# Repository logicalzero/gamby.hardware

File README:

gamby.hardware README
=====================

This repository contains the EAGLE files for the GAMBY LCD/Game shield for
Arduino.

If anyone is interested in porting the design over to a non-proprietary
format (e.g. gEDA), please contact me! 

Design Notes
------------

* Every Arduino pin has a second pad. These pads conform to a uniform .1"
spacing, correcting the .05" offset of the header for digital I/O pins 
8-13 and GND/AREF.

* Although it uses the same pins, this design does not use the ATMega's 
built-in SPI. Since this device does not support bidirectional communication,
using the built-in SPI would have wasted a pin; it would have overly
complicated the traces as well.

* The traces between all of the 'used' Arduino pins and the second pad
have been left uncovered by the bottom soldermask. This is to make it
easier to cut the traces should the user want to rewire things --
to make use of the hardware SPI, for example.

Thanks
------

Thanks go out to my fellow Boston dorkbotter, Tim, for reverse engineering
the surplus LCD module.

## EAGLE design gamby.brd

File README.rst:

gamby.hardware README
=====================

This repository contains the EAGLE files for the GAMBY LCD/Game shield for
Arduino.

If anyone is interested in porting the design over to a non-proprietary
format (e.g. gEDA), please contact me! 

Design Notes
------------

* Every Arduino pin has a second pad. These pads conform to a uniform .1" spacing, correcting the .05" offset of the header for digital I/O pins 8-13 and GND/AREF.

* Although it uses the same pins, this design does not use the ATMega's built-in SPI. Since this device does not support bidirectional communication, using the built-in SPI would have wasted a pin; it would have overly complicated the traces as well.

* The traces between all of the 'used' Arduino pins and the second pad have been left uncovered by the bottom soldermask. This is to make it easier to cut the traces should the user want to rewire things -- to make use of the hardware SPI, for example.

* The sound, D-Pad and buttons have pads for headers; the pads are shorted by a thin, uncovered trace. The sound and inputs can be disabled by cutting this trace, then re-enabled by adding a 2-pin header (3 pins, in the case of sound) and a jumper.

Prototypes
----------

The items in the prototypes directory are the versions that were sent for 
short-run fabrication. The pin-out of the first prototype differs from
the new version. The second prototype has a few minor adjustments made
to make it compatible with the fabrication service (0.1" milling bit,
etc.). 

Datasheets
----------

* LCD: Samsung UG09B63-FLGT4AA using `S6B0755 LCD Controller <http://www.alldatasheet.com/datasheet-pdf/pdf/37866/SAMSUNG/S6B0755.html>`__ or compatible (some features unsupported)
* D-Pad: `ALPS SKQAAA010 4-direction switch <http://www.alldatasheet.com/datasheet-pdf/pdf/329112/ALPS/SKQU.html>`__
* Piezo speaker: `TDK PS1240P02BT <http://www.alldatasheet.com/datasheet-pdf/pdf/349367/TDK/PS1720P02.html>`__
* Backlight LEDs: `Dialight 598-8340-107F <http://www.dialight.com/Assets%5CBrochures_And_Catalogs%5CIndication%5CMDEI5981208RT.pdf>`__

Thanks
------

Thanks go out to my fellow Boston dorkbotter, Tim, for reverse engineering
the surplus LCD module.

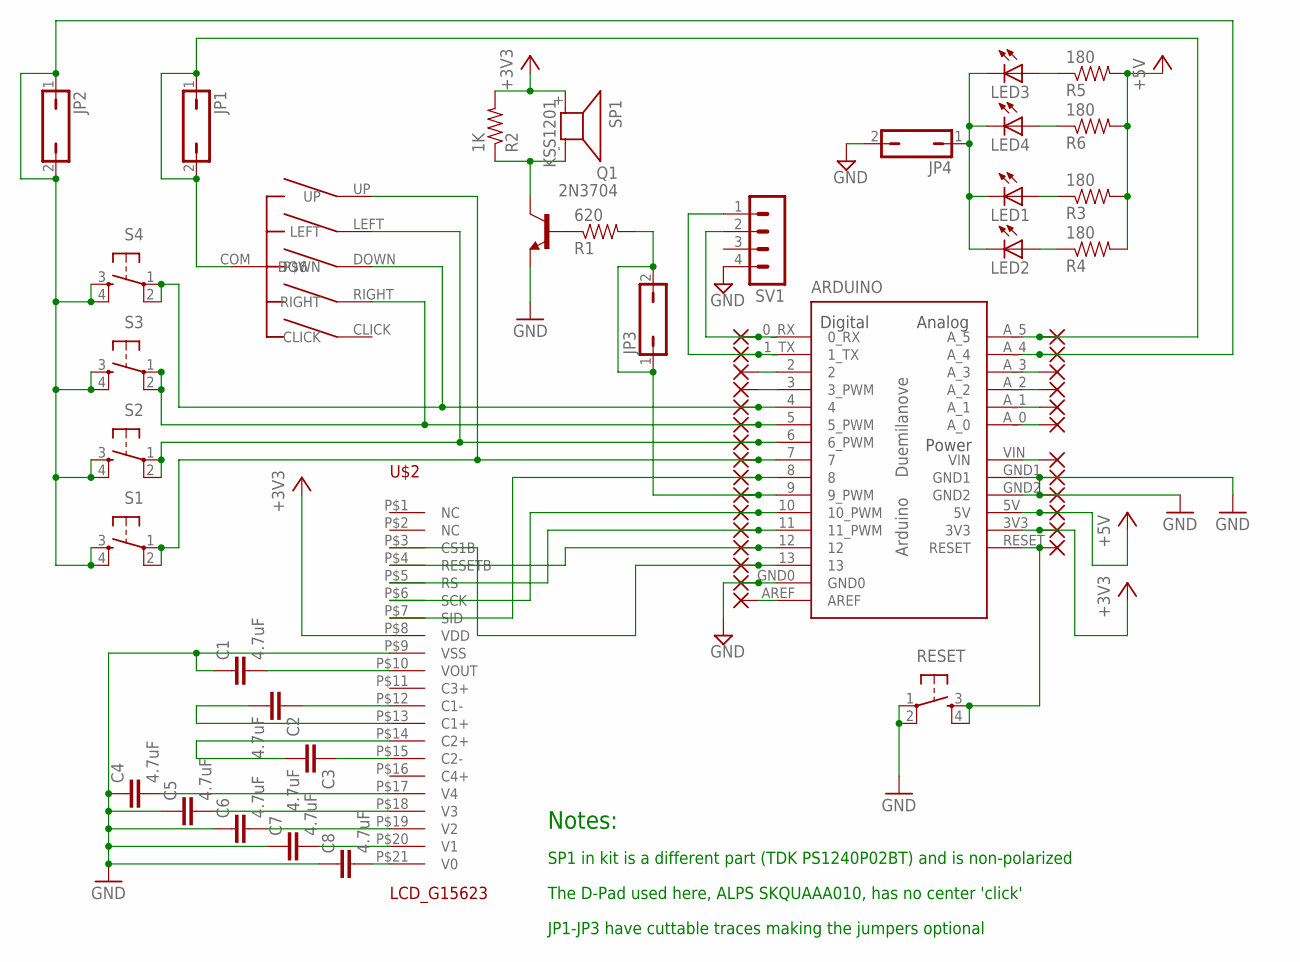
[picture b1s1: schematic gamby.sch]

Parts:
ARDUINO: ARDUINO-USBLONG_PADS_TEXT; SHIELD
C1, C2, C3, C4, C5, C6, C7, C8: 4.7uF; C2.5-2
JP1, JP2, JP3, JP4: JP1Q; JP1
LED1, LED2, LED3, LED4: LEDSMT1206; 1206
PAD_3V3, PAD_5V: WIREPAD1,6/0,9; 1,6/0,9
PAD_A0, PAD_A1, PAD_A2, PAD_A3, PAD_A4, PAD_A5: WIREPAD1,6/0,9; 1,6/0,9
PAD_AREF: WIREPAD1,6/0,9; 1,6/0,9
PAD_D2, PAD_D3, PAD_D4, PAD_D5, PAD_D6, PAD_D7, PAD_D8, PAD_D9, PAD_D10, PAD_D11, PAD_D12, PAD_D13: WIREPAD1,6/0,9; 1,6/0,9
PAD_GND0, PAD_GND1, PAD_GND2: WIREPAD1,6/0,9; 1,6/0,9
PAD_RESET: WIREPAD1,6/0,9; 1,6/0,9
PAD_RX: WIREPAD1,6/0,9; 1,6/0,9
PAD_TX: WIREPAD1,6/0,9; 1,6/0,9
PAD_VIN: WIREPAD1,6/0,9; 1,6/0,9
Q1: 2N3704; TO92
R1: 620; AXIAL-0.3
R2: 1K; AXIAL-0.3
R3, R4, R5, R6: 180; AXIAL-0.3
RESET: TAC_SWITCHPTH; TACTILE-PTH
S1, S2, S3, S4: TAC_SWITCHPTH; TACTILE-PTH
SP1: KSS1201
SV1: MA04-1
U$2: LCD_G15623
U$3: DEV1; DIP

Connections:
0_RX: ARDUINO.0_RX, PAD_RX.1, SV1.2
1_TX: ARDUINO.1_TX, PAD_TX.1, SV1.1
+3V3: ARDUINO.3V3, PAD_3V3.1, R2.P$2 (2), SP1.+ (1), U$2.P$8 (VDD)
+5V: ARDUINO.5V, PAD_5V.1, R3.P$2 (2), R4.P$2 (2), R5.P$2 (2), R6.P$2 (2)
A0: ARDUINO.A_0, PAD_A0.1
A4_BUTTONS: ARDUINO.A_4, JP2.1, JP2.2, PAD_A4.1, S1.3, S1.4, S2.3, S2.4, S3.3, S3.4, S4.3, S4.4
A5_DPAD: ARDUINO.A_5, JP1.1, JP1.2, PAD_A5.1, U$3.COM
BUTTON_A: ARDUINO.7, PAD_D7.1, S1.1, S1.2, U$3.UP
D2: ARDUINO.4, PAD_D4.1, S4.1, S4.2, U$3.DOWN
D3: ARDUINO.9 (9_PWM), JP3.1, JP3.2, PAD_D9.1, R1.P$2 (2)
D4: ARDUINO.5 (5_PWM), PAD_D5.1, S3.1, S3.2, U$3.RIGHT
D5: ARDUINO.6 (6_PWM), PAD_D6.1, S2.1, S2.2, U$3.LEFT
GND: ARDUINO.GND0, ARDUINO.GND1, ARDUINO.GND2, C1.1, C4.1, C5.1, C6.1, C7.1, C8.1, JP4.2, PAD_GND0.1, PAD_GND1.1, PAD_GND2.1, Q1.3 (E), RESET.1, RESET.2, SV1.4, U$2.P$9 (VSS)
unnamed: ARDUINO.8, PAD_D8.1, U$2.P$7 (SID)
unnamed: ARDUINO.10 (10_PWM), PAD_D10.1, U$2.P$6 (SCK)
unnamed: ARDUINO.11 (11_PWM), PAD_D11.1, U$2.P$5 (RS)
unnamed: ARDUINO.12, PAD_D12.1, U$2.P$4 (RESETB)
unnamed: LED1.A, R3.P$1 (1)
unnamed: LED2.A, R4.P$1 (1)
unnamed: JP4.1, LED1.C, LED2.C, LED3.C, LED4.C
unnamed: LED4.A, R6.P$1 (1)
unnamed: ARDUINO.VIN, PAD_VIN.1
unnamed: Q1.2 (C), R2.P$1 (1), SP1.- (2)
unnamed: Q1.1 (B), R1.P$1 (1)
unnamed: ARDUINO.3 (3_PWM), PAD_D3.1
unnamed: C7.2, U$2.P$20 (V1)
unnamed: C5.2, U$2.P$18 (V3)
unnamed: C8.2, U$2.P$21 (V0)
unnamed: C4.2, U$2.P$17 (V4)
unnamed: ARDUINO.13, PAD_D13.1, U$2.P$3 (CS1B)
unnamed: C6.2, U$2.P$19 (V2)
unnamed: ARDUINO.2, PAD_D2.1
unnamed: C3.1, U$2.P$15 (C2-)
unnamed: C3.2, U$2.P$14 (C2+)
unnamed: C2.2, U$2.P$13 (C1+)
unnamed: C2.1, U$2.P$12 (C1-)
unnamed: ARDUINO.A_1, PAD_A1.1
unnamed: C1.2, U$2.P$10 (VOUT)
unnamed: LED3.A, R5.P$1 (1)
unnamed: ARDUINO.RESET, PAD_RESET.1, RESET.3, RESET.4
unnamed: ARDUINO.A_2, PAD_A2.1
unnamed: ARDUINO.A_3, PAD_A3.1
unnamed: ARDUINO.AREF, PAD_AREF.1

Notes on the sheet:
SP1 in kit is a different part (TDK PS1240P02BT) and is non-polarized
The D-Pad used here, ALPS SKQUAAA010, has no center 'click'
Notes:
JP1-JP3 have cuttable traces making the jumpers optional

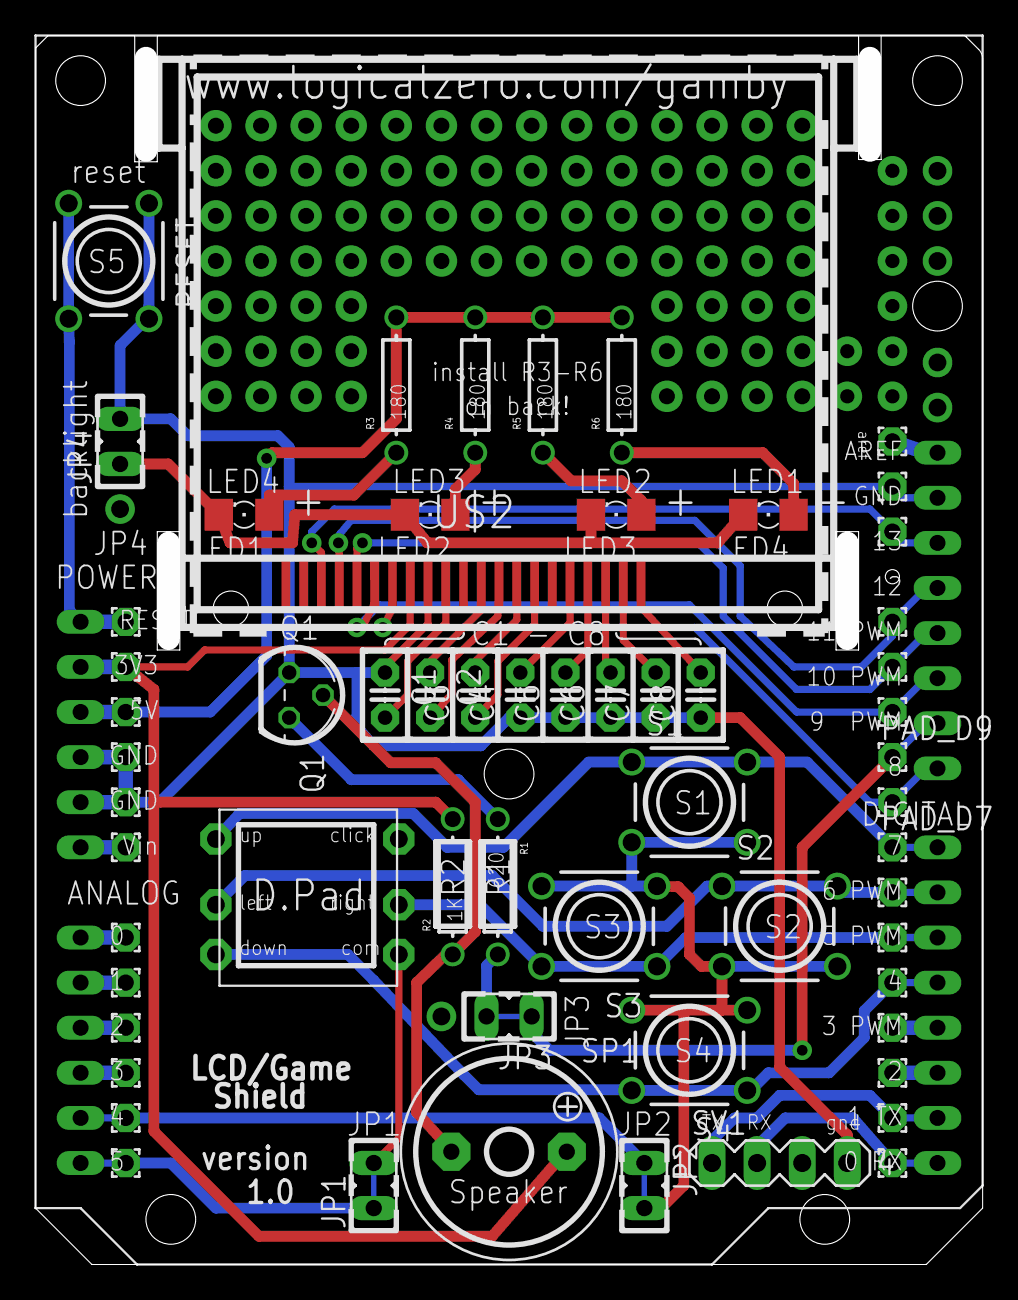
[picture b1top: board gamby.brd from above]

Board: 2 copper layers, 53.3 x 69.2 mm, 61 parts (0 on the bottom side), 43 nets.

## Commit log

2011-05-27 First commit of Gamby Eagle files.
2011-06-26 Prototype version 2
2011-06-26 Board prototype v2
2011-07-07 Inner routing moved to outline layer, aligned two holes with Arduino's.
2011-08-16 Latest revision, plus prototypes (current and first)
2011-09-11 Made drills for secondary pads larger, changed upper slots to notches, other small tweaks.
2011-09-18 Additional small tweaks, added more general-purpose pads.
2011-10-08 Added README to prototypes subdir documenting pin changes between versions; added .rst extension to main README
2011-10-09 Added cuttable shunts bridging input and sound jumpers, making them entirely optional (and addable later)
2011-11-09 Added schematic and board images.
2011-11-12 Added links to data sheets
2011-11-12 Corrections to README
2011-11-12 Added image of schematic, fixed README typo.
2012-02-04 Resaved in new XML-based format.
2012-02-17 Moved and added generic pads, enlarged holes over Uno R3 SCL/SDA pins, increased clearances.
2012-03-04 Re-rendered board images.
2012-03-09 Minor tweaks, mostly cosmetic; added board images with part placement.
2012-03-11 Shifted secondary pads on 12, 13, AREF to improve clearance; added gerbers.
